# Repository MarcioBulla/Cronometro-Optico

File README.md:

# Photogate_V2
I recomend use the second version (improve precise, security, 3D model, interface and schematic): 
https://github.com/Lorxi3D/PhotogateV2

# Objetivo

- [x] Programar o Esp32 com interface para cada experimento, assim facilitando o aluno realizar os experimentos;
- [x] Criar um diagrama e um modelo 3D do Circuito; 
- [x] Modelar 3D todo o projeto, para uma impressão 3D;
- [x] Publica trabalho (doi.org/10.1088/1361-6552/ad6d23).

# Bibliotecas usadas
- `encoder_menu.py`: https://github.com/MarcioBulla/encodermenu
- `rotary.py` e `rotary_irq_esp.py`: https://github.com/miketeachman/micropython-rotary

# Montagem
[Lista de itens e montagem](http://htmlpreview.github.io/?https://github.com/MarcioBulla/Cronometro-Optico/blob/main/manual/Item_List.html)

.png)

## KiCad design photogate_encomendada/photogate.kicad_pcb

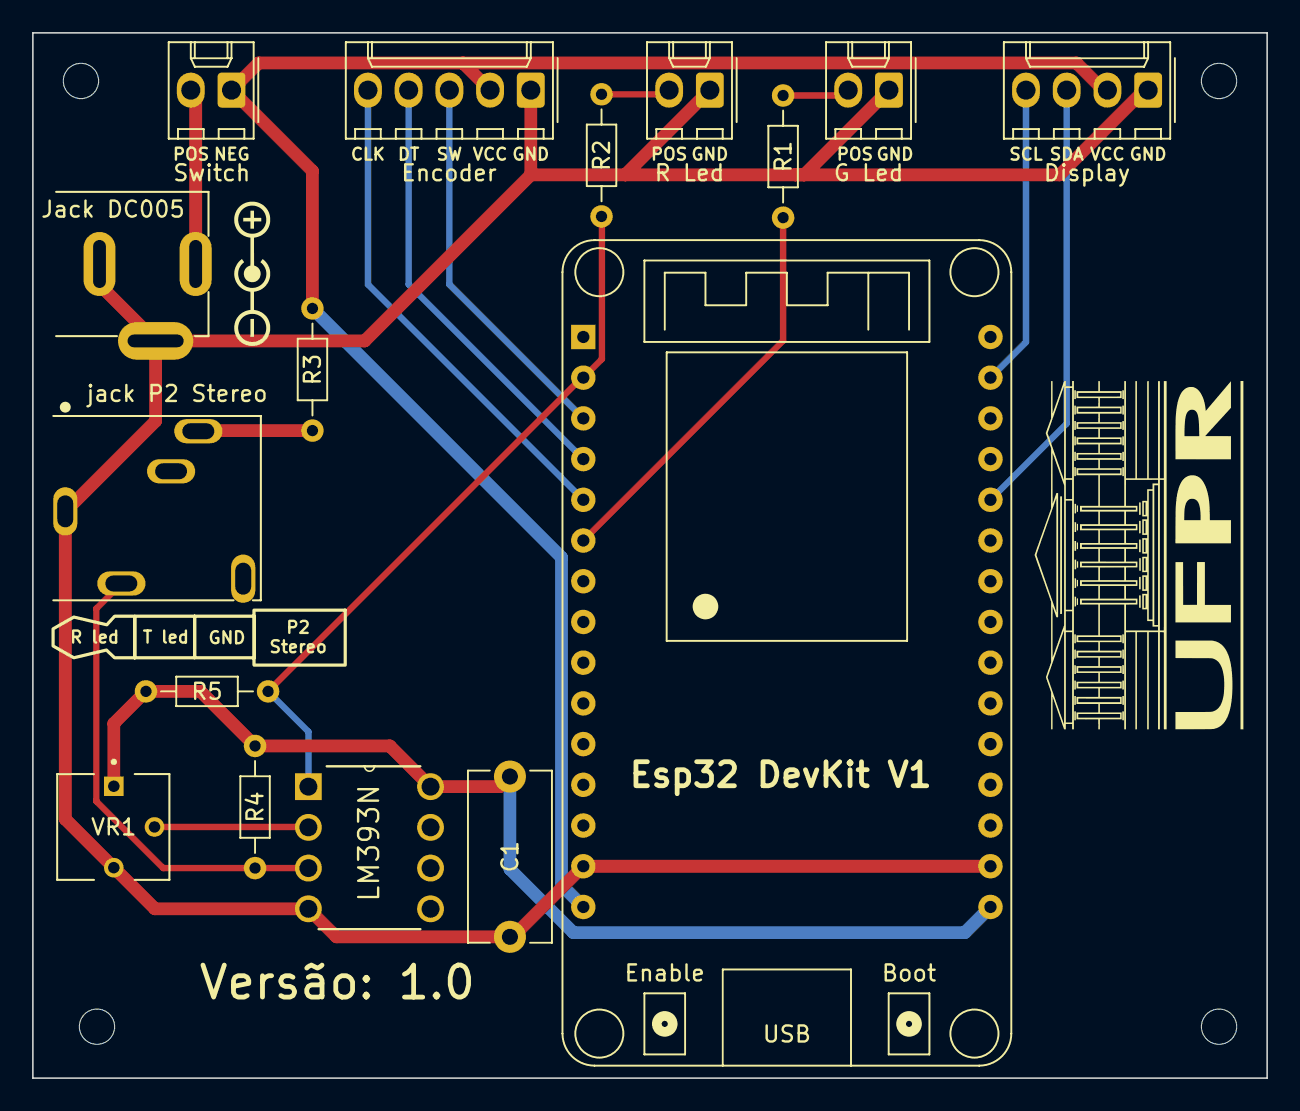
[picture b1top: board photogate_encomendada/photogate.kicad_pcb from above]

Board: 2 copper layers, 77.0 x 65.2 mm, 23 parts (0 on the bottom side), 16 nets.

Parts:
C1: 104k; C_Disc_D10.5mm_W5.0mm_P10.00mm
Display: Conn_01x04_Female; Molex_KK-254_AE-6410-04A_1x04_P2.54mm_Vertical
Encoder: Conn_01x05_Female; Molex_KK-254_AE-6410-05A_1x05_P2.54mm_Vertical
Esp32 DevKit V1: ESP32_DevKit_V1_DOIT; esp32_devkit_v1_doit
Furo Central: MountingHole_2.2mm_M2
Furo Inferior1, Furo Inferior2: MountingHole_2.2mm_M2
Furo Superior: MountingHole_2.2mm_M2
G Led: Conn_01x02_Female; Molex_KK-254_AE-6410-02A_1x02_P2.54mm_Vertical
Jack DC005: DC-005; NINIGI_DC-005
LM393N: LM393N1; LM393N
P2 3poles: LOGO; P2_3poles
R1, R2, R3, R5: 100; R_Axial_DIN0204_L3.6mm_D1.6mm_P7.62mm_Horizontal
R4: 10k; R_Axial_DIN0204_L3.6mm_D1.6mm_P7.62mm_Horizontal
R Led: Conn_01x02_Female; Molex_KK-254_AE-6410-02A_1x02_P2.54mm_Vertical
Switch: Conn_01x02_Female; Molex_KK-254_AE-6410-02A_1x02_P2.54mm_Vertical
UFPR: UFPR
VR1: 3362P-1-103; TRIM_3362P-1-103
jack P2 Stereo: SJ1-3515N; CUI_SJ1-3515N
polarity: Symbol; Polarity_Center_Positive_9mm_SilkScreen

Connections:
/CLK: Encoder.5, Esp32 DevKit V1.5 (IO35)
/D0: Esp32 DevKit V1.2 (SENSOR_VP), LM393N.1 (Output), R2.1, R5.1
/DT: Encoder.4, Esp32 DevKit V1.4 (IO34)
/FUNC_LED: G Led.2, R1.2
/PHOTODIODE: LM393N.3 (+), R4.2, jack P2 Stereo.2
/SCL: Display.4, Esp32 DevKit V1.29 (IO22)
/SDA: Display.3, Esp32 DevKit V1.26 (IO21)
/SW: Encoder.3, Esp32 DevKit V1.3 (SENSOR_VN)
GND: C1.2, Display.1, Encoder.1, Esp32 DevKit V1.14 (GND), Esp32 DevKit V1.17 (GND), G Led.1, Jack DC005.2, Jack DC005.3, LM393N.4 (V-), R Led.1, VR1.3, jack P2 Stereo.1
unnamed: C1.1, Esp32 DevKit V1.16 (3V3), LM393N.8 (V+), R4.1, R5.2, VR1.1
unnamed: Esp32 DevKit V1.6 (IO32), R1.1
unnamed: Display.2, Encoder.2, Esp32 DevKit V1.15 (VIN), R3.1, Switch.1
unnamed: Jack DC005.4, Switch.2
unnamed: LM393N.2 (-), VR1.2
unnamed: R2.2, R Led.2
unnamed: R3.2, jack P2 Stereo.3

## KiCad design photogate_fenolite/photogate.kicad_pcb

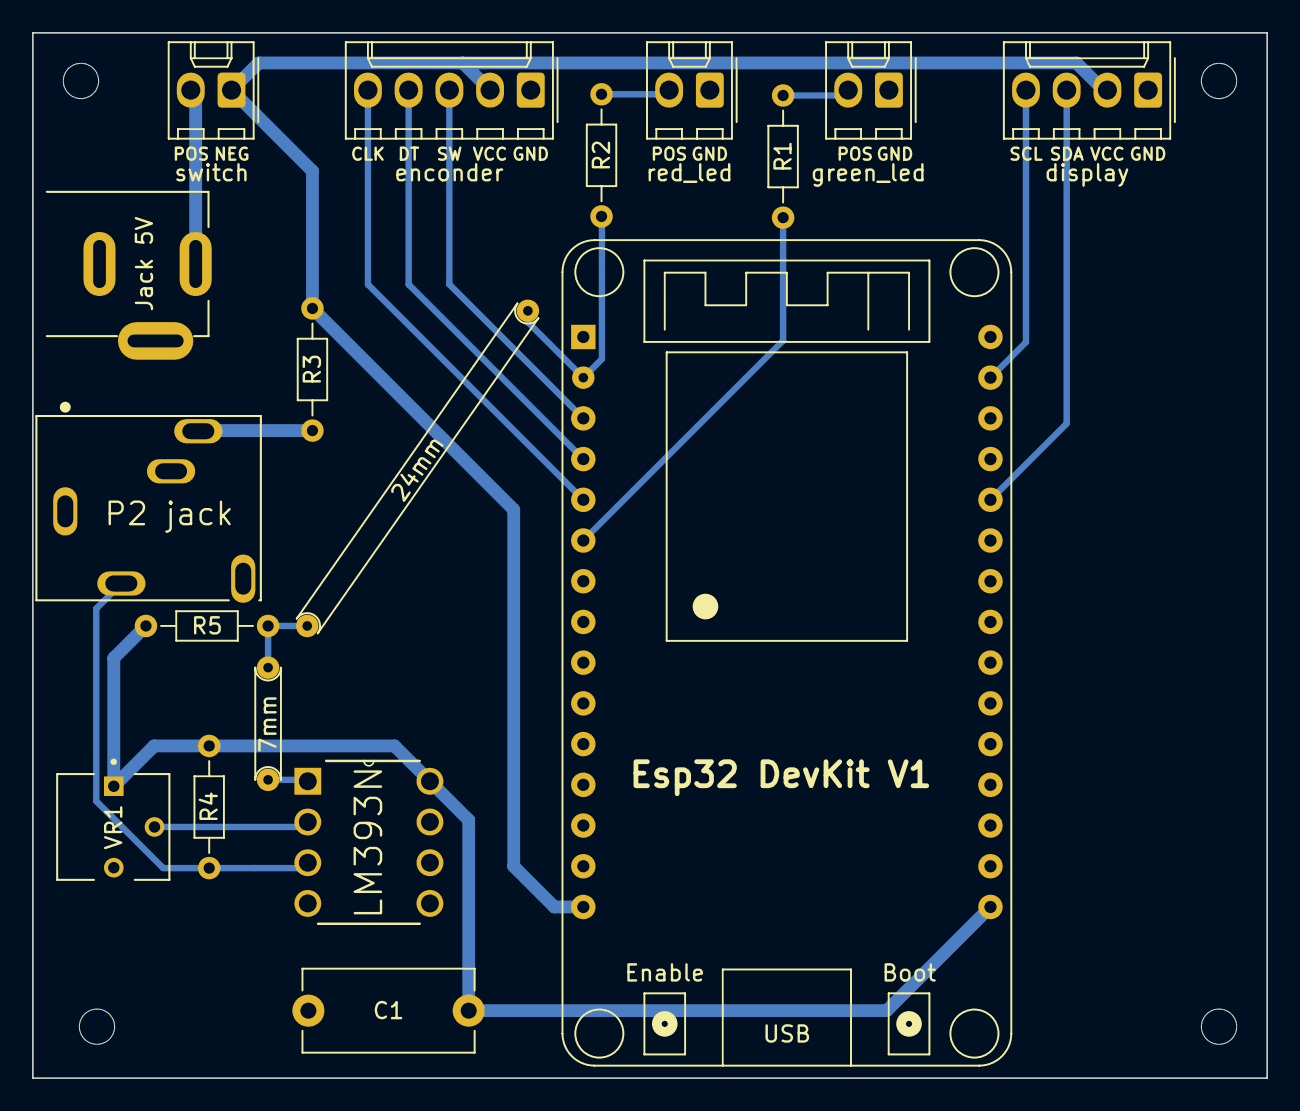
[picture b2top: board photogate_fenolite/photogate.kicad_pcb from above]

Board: 2 copper layers, 77.0 x 65.2 mm, 22 parts (0 on the bottom side), 18 nets.

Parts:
5mm: Jumper_7mm; Jumper_7mm_blue
24mm: Jumper_24mm; Jumper_24mm_blue
C1: 104k; C_Disc_D10.5mm_W5.0mm_P10.00mm
Esp32 DevKit V1: ESP32_DevKit_V1_DOIT; esp32_devkit_v1_doit
Furo Central: MountingHole_2.2mm_M2
Furo Inferior1, Furo Inferior2: MountingHole_2.2mm_M2
Furo Superior: MountingHole_2.2mm_M2
Jack 5V: DC-005
LM393N: LM393N1; LM393N
P2 jack: SJ1-3515N; CUI_SJ1-3515N
R1, R2, R3, R5: 100; R_Axial_DIN0204_L3.6mm_D1.6mm_P7.62mm_Horizontal
R4: 10k; R_Axial_DIN0204_L3.6mm_D1.6mm_P7.62mm_Horizontal
VR1: 3362P-1-103; trimpot_3362P
display: Conn_01x04_Female; Molex_KK-254_AE-6410-04A_1x04_P2.54mm_Vertical
enconder: Conn_01x05_Female; Molex_KK-254_AE-6410-05A_1x05_P2.54mm_Vertical
green_led: Conn_01x02_Female; Molex_KK-254_AE-6410-02A_1x02_P2.54mm_Vertical
red_led: Conn_01x02_Female; Molex_KK-254_AE-6410-02A_1x02_P2.54mm_Vertical
switch: Conn_01x02_Female; Molex_KK-254_AE-6410-02A_1x02_P2.54mm_Vertical

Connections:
/CLK: Esp32 DevKit V1.5 (IO35), enconder.5
/DT: Esp32 DevKit V1.4 (IO34), enconder.4
/FUNC_LED: R1.2, green_led.2
/PHOTODIODE: LM393N.3 (+), P2 jack.2, R4.2
/SCL: Esp32 DevKit V1.29 (IO22), display.4
/SDA: Esp32 DevKit V1.26 (IO21), display.3
/SW: Esp32 DevKit V1.3 (SENSOR_VN), enconder.3
GND: C1.2, Esp32 DevKit V1.14 (GND), Esp32 DevKit V1.17 (GND), Jack 5V.2, Jack 5V.3, LM393N.4 (V-), P2 jack.1, VR1.3, display.1, enconder.1, green_led.1, red_led.1
unnamed: C1.1, Esp32 DevKit V1.16 (3V3), LM393N.8 (V+), R4.1, R5.1, VR1.1
unnamed: 24mm.2 (B), Esp32 DevKit V1.2 (SENSOR_VP), R2.1
unnamed: Esp32 DevKit V1.6 (IO32), R1.1
unnamed: Esp32 DevKit V1.15 (VIN), R3.1, display.2, enconder.2, switch.1
unnamed: 5mm.1 (A), LM393N.1 (Output)
unnamed: Jack 5V.4, switch.2
unnamed: LM393N.2 (-), VR1.2
unnamed: P2 jack.3, R3.2
unnamed: R2.2, red_led.2
unnamed: 5mm.2 (B), 24mm.1 (A), R5.2

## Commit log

2022-11-12 Teste terminal (Problema range encoder)
2022-11-12 Interface funcionando corretamente
2022-11-12 Teste de funções (função blink)
2022-11-12 remove redundance e organizando
2022-11-14 Mais informações sobre o projeto
2022-11-14 Correção get_iterger e reverse
2022-11-14 Atualização do projeto
2022-11-15 Primeira versão cronometro
2022-11-16 Pedulo faltando historico
2022-11-16 1v do pendulo
2022-11-16 att README.md
2022-11-22 Update Pend
2022-11-22 Energia Mec completo
2022-11-23 upgrade Historioco
2022-11-23 Mola
2022-11-23 Calibragem completa
2022-11-23 Priveira verição para Oled
2022-11-25 mais acabamentos para diplay oled
2022-11-27 Otimização cronos e historico
2022-12-02 Circuito em uma PCI
2022-12-02 Correção link para lista de materiais
2022-12-02 remove UFPR list
2022-12-02 Add resitor green led
2022-12-03 Correção português
2022-12-04 Melhoras na placa
2022-12-04 add intruções na PCI
2022-12-07 Upgrade Display oled 0.96inc to Display lcd 2004
2022-12-11 att designe PCB
2022-12-14 add msg concluido e simplificação do código
2022-12-14 Add connector para switch
2022-12-15 Trocar connector jst para KK
2022-12-15 Demonstração da placa
2022-12-15 correção
2022-12-17 Ultimos ajustes
2022-12-21 novas fotos
2023-02-19 Sem Colaboração até agora
2023-02-19 otimização
2023-03-07 organizando
2023-03-07 resolve links README.md
2023-03-21 Placas de fenolite e perfurada acabadas
2024-09-16 update README.md and add suggestion
2024-09-16 explain improviment
2025-08-14 remove contribution html from Item_list.html
